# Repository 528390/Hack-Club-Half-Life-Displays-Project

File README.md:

Glass Collection LED Lighting System

What is this project?
This project is a custom-designed printed circuit board (PCB) that provides lighting for a glass collection cabinet. It combines white LEDs and RGB lighting to illuminate the collection while allowing different lighting modes.

How does this project work?
The lighting system uses a XIAO RP2040 microcontroller to control two 5mm white LEDs and a 5mm RGB LED. A push button allows the user to switch between lighting modes, and a 10kΩ potentiometer is included for brightness adjustment. The schematic and PCB layout were designed in KiCad, and the firmware will be written using Arduino.

List of hardware components:

- XIAO RP2040 microcontroller(1x)
- 5 mm white LEDs(2x)
- 5 mm common-cathode RGB LED(1x)
- Resistors(5x)
- Push button (1x)
- 10kΩ potentiometer (1x)
- Custom PCB designed with KiCad

My Project Status:
I have finished designing the schematic and PCB layout in KiCad. The firmware and physical assembly are not yet complete because the parts have not been shipped. My goal is to finish the design, test the lighting system on the physical hardware, and prepare the files for manufacturing.

Repository Contents:

- BOM.md — Bill of materials
- JOURNAL.md — Project progress and analysis
- Schematic and PCB layout files designed in KiCad
- Gerber and drill files for PCB manufacturing
- Arduino firmware

PCB Design:
https://github.com/528390/Hack-Club-Half-Life-Displays-Project/blob/main/PCB%20layout.png
https://github.com/528390/Hack-Club-Half-Life-Displays-Project/blob/main/wired%20PCB.png

PCB Schematic Layout:
https://github.com/528390/Hack-Club-Half-Life-Displays-Project/blob/main/schematic%20layout.png

PCB Images

Bill of Materials (BOM) Table

| Part / Material | Quantity | Unit Price | Buying Link |
|---|---:|---:|---|
| XIAO RP2040 | 1 | $5.00 | [Seeed Studio](https://www.seeedstudio.com/Seeed-Studio-XIAO-RP2040-Pre-Soldered-p-6333.html) |
| 5 mm white LED | 2 | $0.40 | [MicroCenter](https://www.microcenter.com/product/456219/adafruit-industries-super-bright-white-5mm-led-25-pack) |
| 5 mm common-cathode RGB LED | 1 | $1.49 | [TinkerSphere](https://tinkersphere.com/standard-leds/46-rgb-led.html) |
| Resistors(100Ω) | 4 | $0.08 | [SparkFun Electronics](https://www.sparkfun.com/resistor-100-ohm-1-4-watt-pth-20-pack-thick-leads.html) |
| Resistor(270Ω) | 1 | $0.05 | [Jameco](https://www.jameco.com/z/CF1-4W271JRC-Jameco-Valuepro-Resistor-Carbon-Film-270-Ohm-1-4-Watt-5-_690726.html) |
| Push button | 1 | $0.13 | [DigiKey](https://www.digikey.com/en/products/detail/te-connectivity-alcoswitch-switches/1825910-6/1632536) |
| 10kΩ potentiometer | 1 | $1.25 | [SparkFun Electronics](https://www.sparkfun.com/rotary-potentiometer-linear-10k-ohm.html) |
| Custom PCB | 1 | $4.00 | [JLCPCB](https://jlcpcb.com/) |

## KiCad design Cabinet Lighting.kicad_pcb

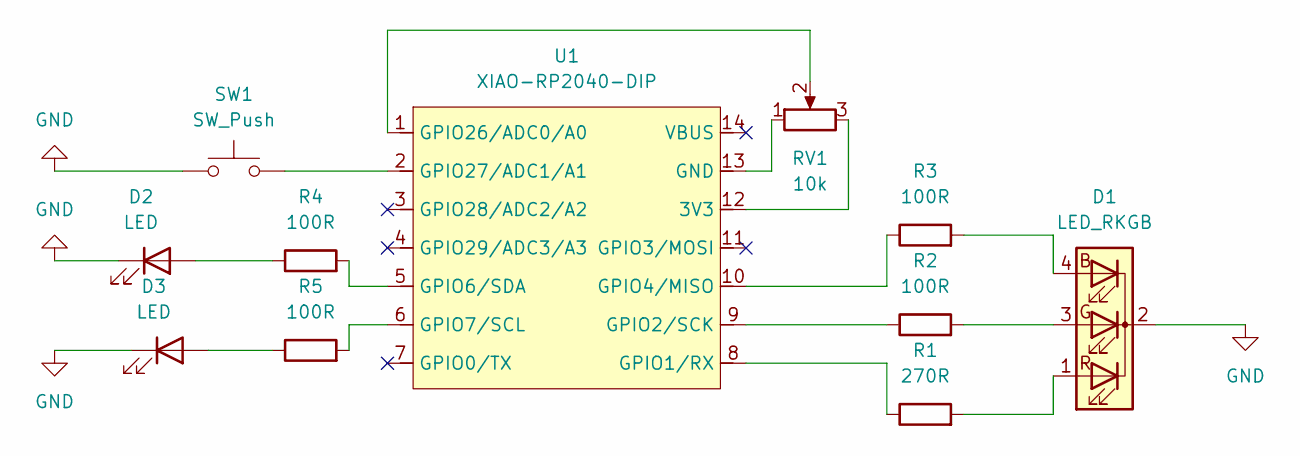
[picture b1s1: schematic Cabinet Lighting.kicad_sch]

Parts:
D1: LED_RKGB; LED_D5.0mm-4_RGB
D2, D3: LED; LED_D5.0mm
R1: 270R; R_Axial_DIN0207_L6.3mm_D2.5mm_P7.62mm_Horizontal
R2, R3, R4, R5: 100R; R_Axial_DIN0207_L6.3mm_D2.5mm_P7.62mm_Horizontal
RV1: 10k; Potentiometer_Alps_RK09K_Single_Vertical
SW1: SW_Push; SW_PUSH_6mm_H4.3mm
U1: XIAO-RP2040-DIP

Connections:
GND: D1.2 (K), D2.1 (K), D3.1 (K), SW1.1
unnamed: D1.4 (BA), R3.2
unnamed: D1.3 (GA), R2.2
unnamed: D1.1 (RA), R1.2
unnamed: D2.2 (A), R4.1
unnamed: D3.2 (A), R5.1
unnamed: RV1.3, U1.12 (3V3)
unnamed: RV1.1, U1.13 (GND)
unnamed: R1.1, U1.8 (GPIO1/RX)
unnamed: R2.1, U1.9 (GPIO2/SCK)
unnamed: R3.1, U1.10 (GPIO4/MISO)
unnamed: R4.2, U1.5 (GPIO6/SDA)
unnamed: R5.2, U1.6 (GPIO7/SCL)
unnamed: RV1.2, U1.1 (GPIO26/ADC0/A0)
unnamed: SW1.2, U1.2 (GPIO27/ADC1/A1)

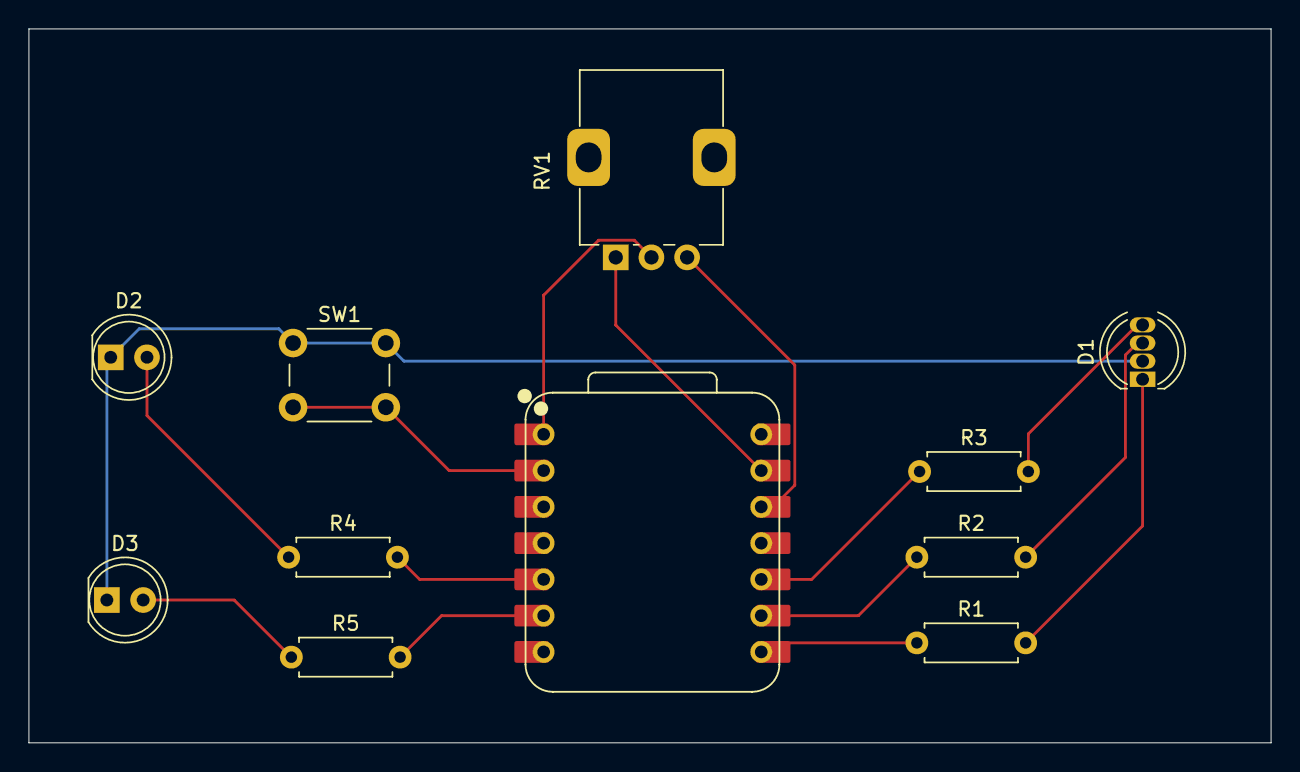
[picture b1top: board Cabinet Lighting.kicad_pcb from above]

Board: 2 copper layers, 87.0 x 50.0 mm, 11 parts (0 on the bottom side), 15 nets.
